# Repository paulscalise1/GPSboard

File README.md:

# GPS Board v3.0 r1.1

This board is designed for ECEN-435 at the University of Nebraska-Lincoln (Scott Campus).
GPS coordinates will print via CAN every 4 seconds. All GPS information sent over CAN is ASCII encoded.
To obtain a lock, you must have a direct line of sight to the sky!!
For CAN transmissions to work properly, the CAN resistor header (CAN R) must be shorted, allowing for proper termination.

Example Messages:

Message with no GPS Lock: ```LA00.00NLO000.0E```

Message with GPS Lock: ```LA41.14NLO096.0W```

## CAN Parameters

CAN is enabled by default at 100 kbps with the following parameters.

Bit Timing Parameters:
System Clock --> ```HSI48```
Prescaler (for Time Quantum) --> ```120```
Time Quanta in Bit Segment 1 --> ```2 Times```
Time Quanta in Bit Segment 2 --> ```1 Time```
ReSynchronization Jump Width --> ```1 Time```

All Basic Parameters --> ```Disabled```

Advanced Parameters:
Operating Mode --> ```Normal```

## Firmware

The entire CubeIDE project for the STM32F042F4P6 is found in the Firmware folder.

## Connections

## Board

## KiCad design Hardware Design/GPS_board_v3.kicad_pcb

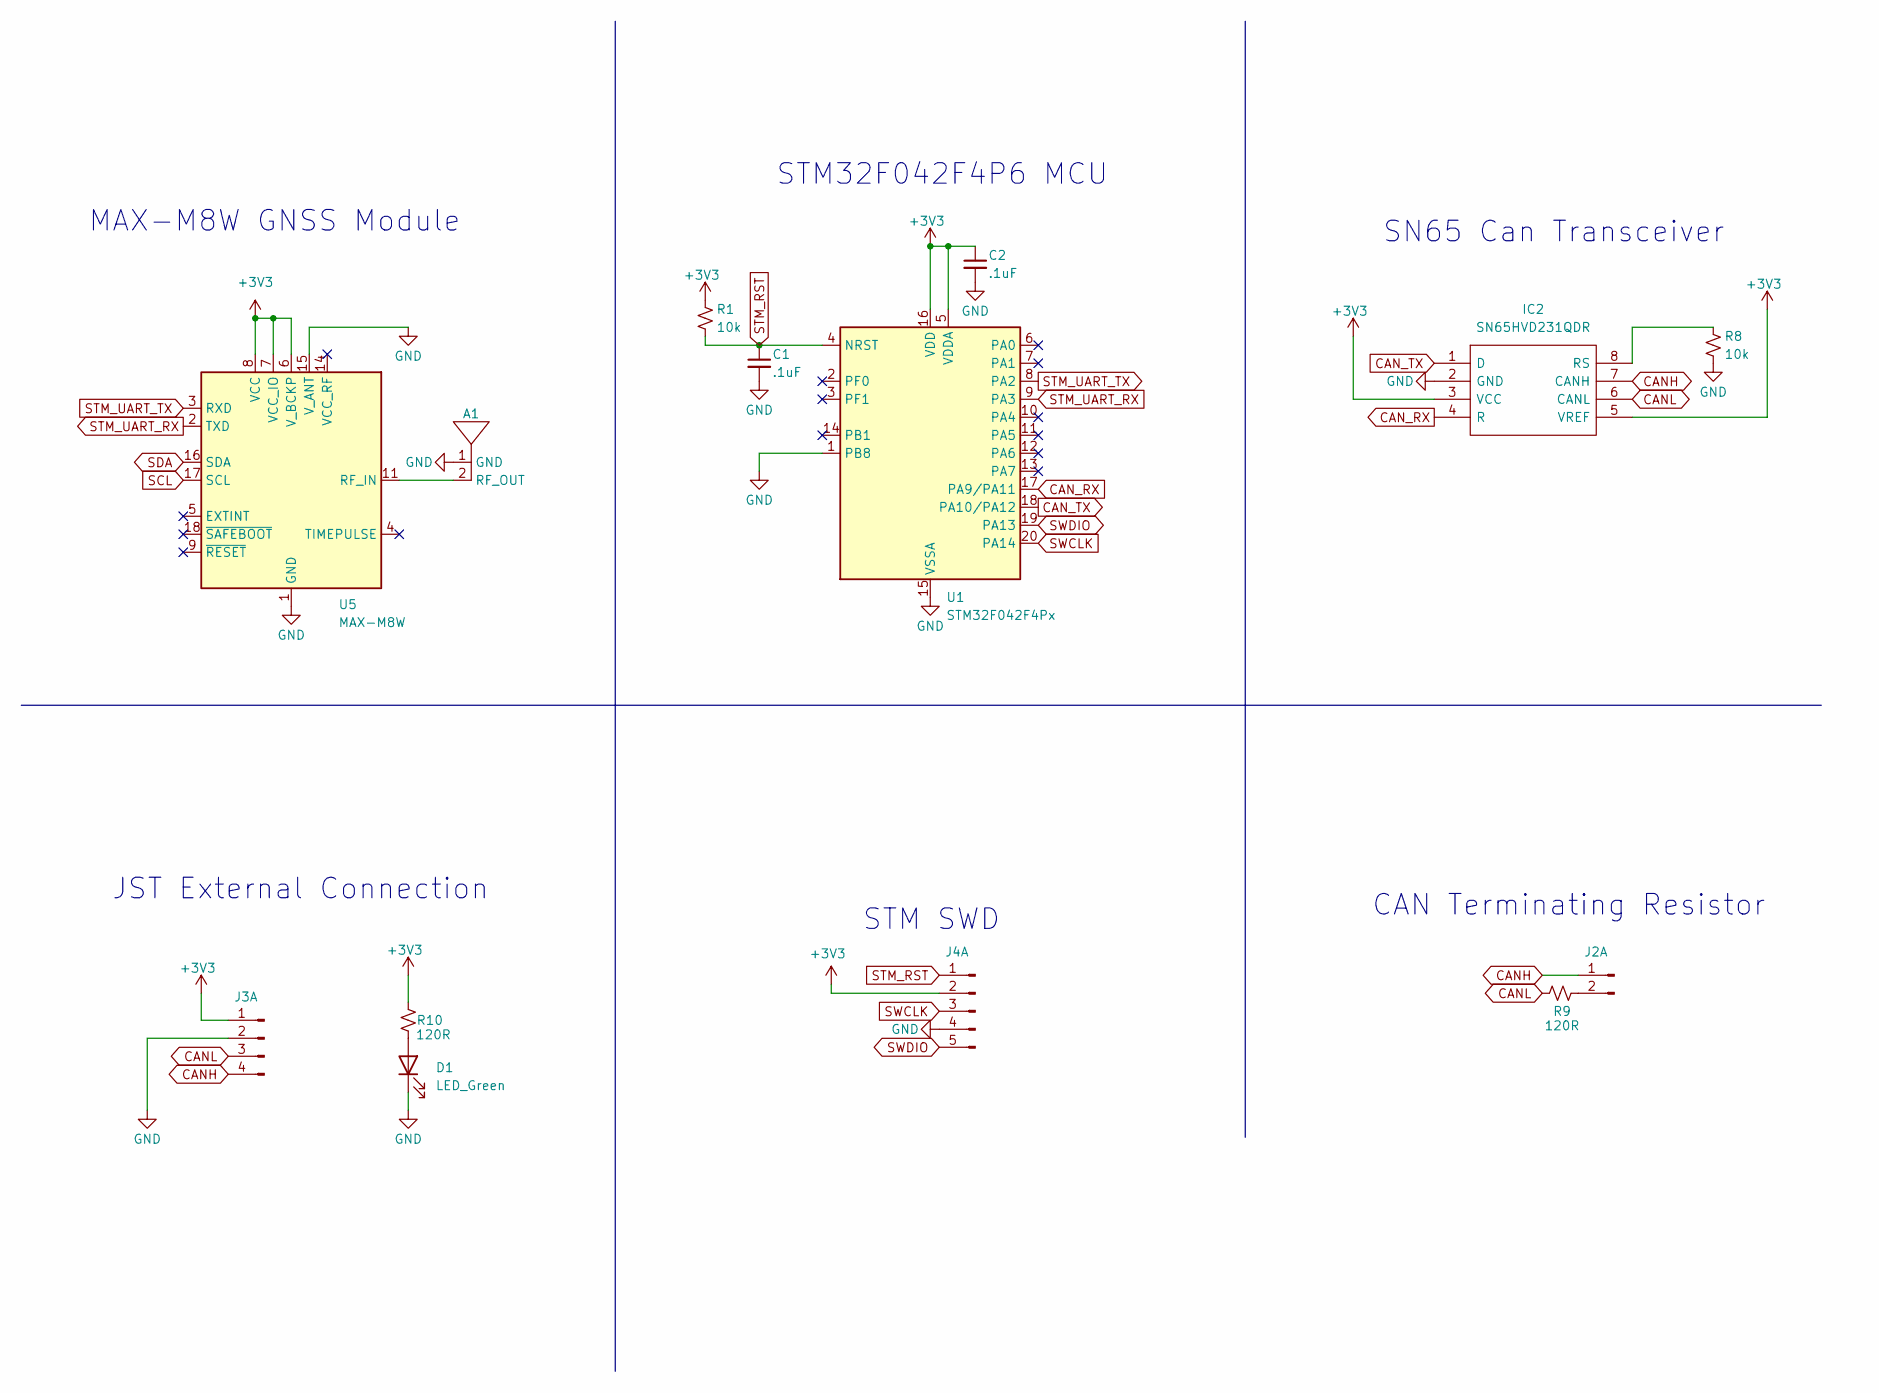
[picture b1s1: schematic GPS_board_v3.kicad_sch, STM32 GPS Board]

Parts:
A1: L000953-01
C1, C2: .1uF; C_0805_2012Metric
D1: LED_Green; LED_0805_2012Metric_Pad1.15x1.40mm_HandSolder
IC2: SN65HVD231QDR; SOIC127P600X175-8N; Mouser Part Number 595-SN65HVD231QDR
J2: PinHeader_1x02_P2.54mm_Vertical
J3: PinHeader_1x04_P2.54mm_Vertical
J4: PinHeader_1x05_P2.54mm_Vertical
R1, R8: 10k; R_0805_2012Metric_Pad1.20x1.40mm_HandSolder
R9, R10: 120R; R_0805_2012Metric_Pad1.20x1.40mm_HandSolder
U1: STM32F042F4Px; TSSOP-20_4.4x6.5mm_P0.65mm
U5: MAX-M8W; ublox_MAX

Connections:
+3V3: C2.1, IC2.3 (VCC), IC2.5 (VREF), J3.1, J4.2, R1.1, R10.2, U1.5 (VDDA), U1.16 (VDD), U5.6 (V_BCKP), U5.7 (VCC_IO), U5.8 (VCC)
CANH: IC2.7 (CANH), J2.1, J3.4
CANL: IC2.6 (CANL), J3.3, R9.1
CAN_RX: IC2.4 (R), U1.17 (PA9/PA11)
CAN_TX: IC2.1 (D), U1.18 (PA10/PA12)
GND: A1.1 (GND), C1.2, C2.2, D1.1 (K), IC2.2 (GND), J3.2, J4.4, R8.2, U1.1 (PB8), U1.15 (VSSA), U5.1 (GND), U5.10 (GND), U5.12 (GND), U5.15 (V_ANT)
unnamed: A1.2 (RF_OUT), U5.11 (RF_IN)
unnamed: D1.2 (A), R10.1
unnamed: IC2.8 (RS), R8.1
unnamed: J2.2, R9.2
SCL: U5.17 (SCL)
SDA: U5.16 (SDA)
STM_RST: C1.1, J4.1, R1.2, U1.4 (NRST)
STM_UART_RX: U1.9 (PA3), U5.2 (TXD)
STM_UART_TX: U1.8 (PA2), U5.3 (RXD)
SWCLK: J4.3, U1.20 (PA14)
SWDIO: J4.5, U1.19 (PA13)

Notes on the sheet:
MAX-M8W GNSS Module
STM32F042F4P6 MCU
CAN Terminating Resistor
STM SWD
JST External Connection
SN65 Can Transceiver

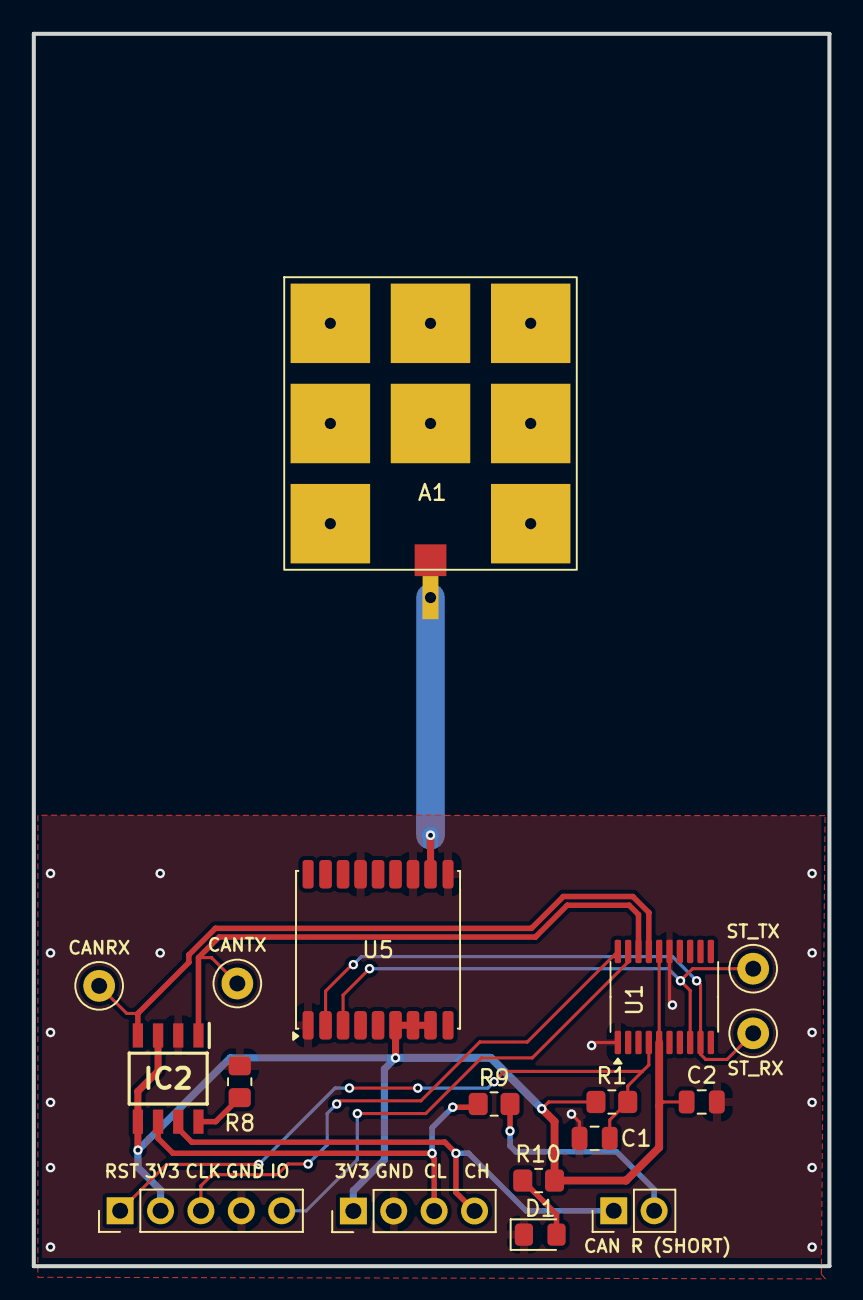
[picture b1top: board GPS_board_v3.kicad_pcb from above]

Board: 2 copper layers, 50.0 x 77.5 mm, 14 parts (0 on the bottom side), 15 nets.

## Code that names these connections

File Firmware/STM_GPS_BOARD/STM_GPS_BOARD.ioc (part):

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Mcu.Name=STM32F042F4Px
Mcu.Package=TSSOP20
Mcu.UserName=STM32F042F4Px
PA11.Mode=CAN_Activate
PA11.Signal=CAN_RX
PA12.Mode=CAN_Activate
PA12.Signal=CAN_TX
PA13.Mode=Serial_Wire
PA13.Signal=SYS_SWDIO
PA14.Mode=Serial_Wire
PA14.Signal=SYS_SWCLK
PA2.Mode=Asynchronous
PA2.Signal=USART2_TX
PA3.Mode=Asynchronous
PA3.Signal=USART2_RX
RCC.SYSCLKFreq_VALUE=48000000
RCC.SYSCLKSource=RCC_SYSCLKSOURCE_HSI48
board=custom

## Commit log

2025-08-14 added STM32 firmware files
2025-08-18 final updated board + prod files
2025-08-18 readme update
2025-12-01 added antenna ground pads to F_Paste for stencil
2026-06-23 Added testing headers.
